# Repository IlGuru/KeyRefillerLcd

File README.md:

# KeyRefillerLcd
Progetto Key Refiller con LCD

KEY_REFILLER_LCD.X
  Cartella di lavoro di "Microchip MPLAB.X IDE" del firmware
Kicad
  Cartella di lavoro del progetto Kicad del PCB

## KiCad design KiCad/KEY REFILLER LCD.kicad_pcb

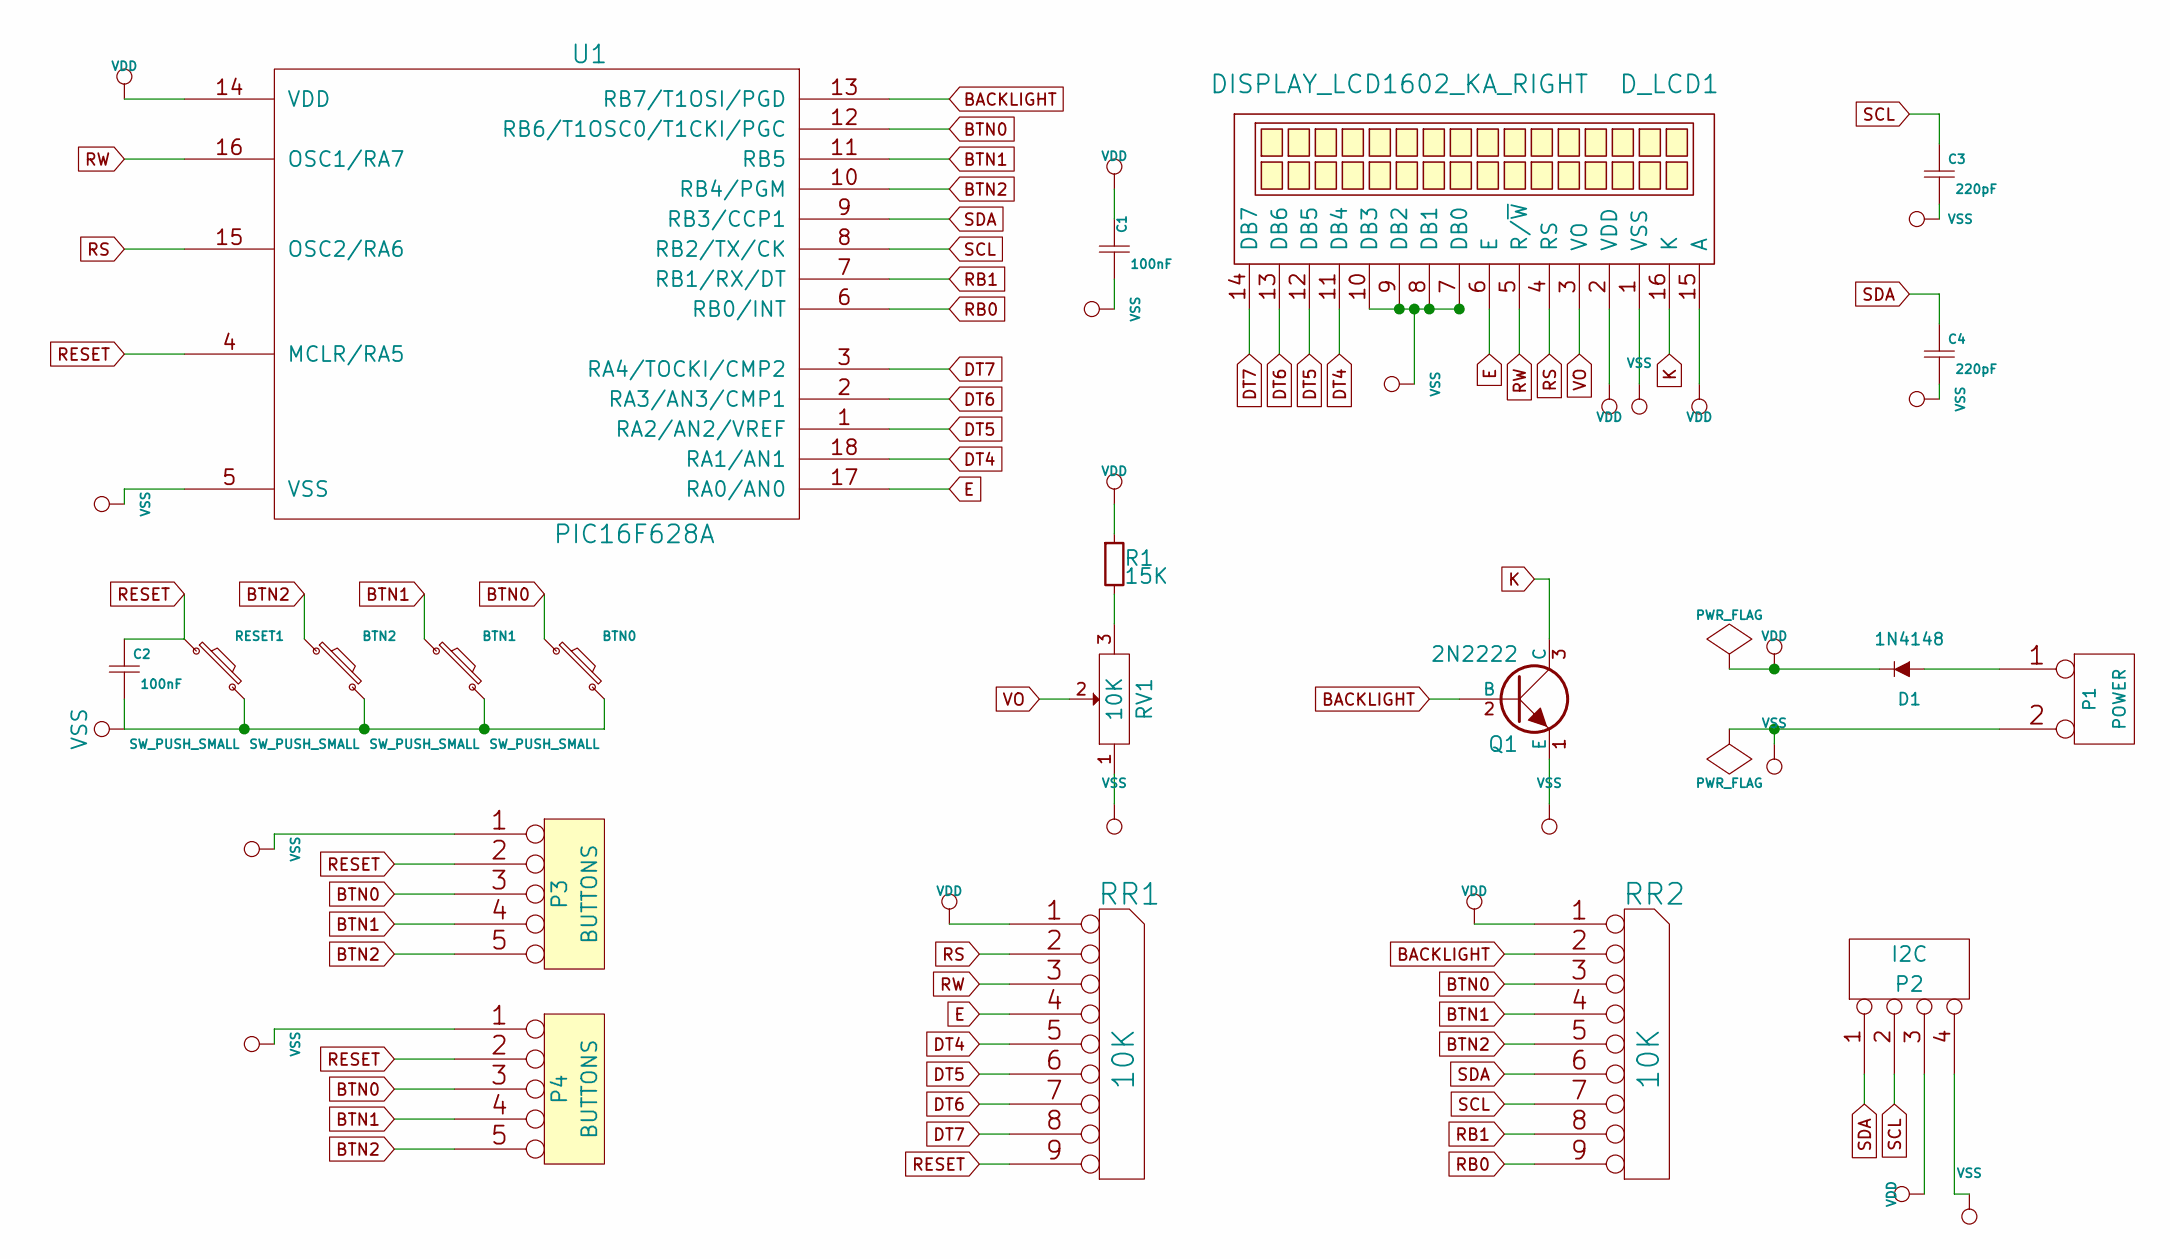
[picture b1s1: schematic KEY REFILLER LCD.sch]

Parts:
BTN0, BTN1, BTN2: SW_PUSH_SMALL
C1, C2: 100nF; C_Disc_D6_P5
C3, C4: 220pF; C_Disc_D6_P5
D1: 1N4148; Diode_DO-35_SOD27_Horizontal_RM10
D_LCD1: DISPLAY_LCD1602_KA_RIGHT; RC1602A
P1: POWER; Pin_Header_Straight_1x02
P2: I2C; Pin_Header_Straight_1x04
P3, P4: BUTTONS; Pin_Header_Straight_1x05
Q1: 2N2222; TO-18_3Pin
R1: 15K; Resistor_Horizontal_RM15mm
RESET1: SW_PUSH_SMALL
RR1, RR2: 10K; r_sil_9
RV1: 10K; POT_4x2
U1: PIC16F628A; DIP-18_W7.62mm_LongPads

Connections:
BACKLIGHT: Q1.2 (B), RR2.2, U1.13 (RB7/T1OSI/PGD)
BTN0: BTN0.1, P3.3, P4.3, RR2.3, U1.12 (RB6/T1OSC0/T1CKI/PGC)
BTN1: BTN1.1, P3.4, P4.4, RR2.4, U1.11 (RB5)
BTN2: BTN2.1, P3.5, P4.5, RR2.5, U1.10 (RB4/PGM)
DT4: D_LCD1.11 (DB4), RR1.5, U1.18 (RA1/AN1)
DT5: D_LCD1.12 (DB5), RR1.6, U1.1 (RA2/AN2/VREF)
DT6: D_LCD1.13 (DB6), RR1.7, U1.2 (RA3/AN3/CMP1)
DT7: D_LCD1.14 (DB7), RR1.8, U1.3 (RA4/TOCKI/CMP2)
E: D_LCD1.6 (E), RR1.4, U1.17 (RA0/AN0)
K: D_LCD1.16 (K), Q1.3 (C)
unnamed: D1.2 (A), P1.1
unnamed: R1.2, RV1.3
RB0: RR2.9, U1.6 (RB0/INT)
RB1: RR2.8, U1.7 (RB1/RX/DT)
RESET: C2.1, P3.2, P4.2, RESET1.1, RR1.9, U1.4 (MCLR/RA5)
RS: D_LCD1.4 (RS), RR1.2, U1.15 (OSC2/RA6)
RW: D_LCD1.5 (R/~W), RR1.3, U1.16 (OSC1/RA7)
SCL: C3.1, P2.2, RR2.7, U1.8 (RB2/TX/CK)
SDA: C4.1, P2.1, RR2.6, U1.9 (RB3/CCP1)
VDD: C1.1, D1.1 (K), D_LCD1.2 (VDD), D_LCD1.15 (A), P2.3, R1.1, RR1.1 (COM), RR2.1 (COM), U1.14 (VDD)
VO: D_LCD1.3 (VO), RV1.2
VSS: BTN0.2, BTN1.2, BTN2.2, C1.2, C2.2, C3.2, C4.2, D_LCD1.1 (VSS), D_LCD1.7 (DB0), D_LCD1.8 (DB1), D_LCD1.9 (DB2), D_LCD1.10 (DB3), P1.2 (PM), P2.4, P3.1, P4.1, Q1.1 (E), RESET1.2, RV1.1, U1.5 (VSS)

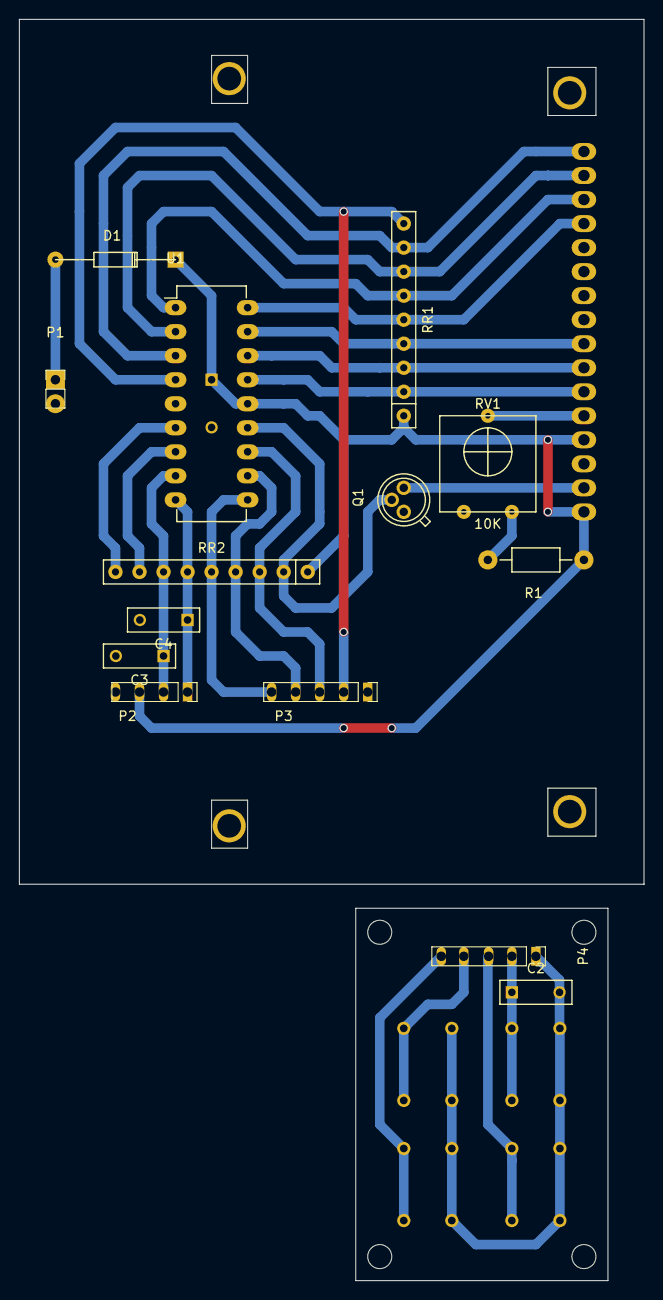
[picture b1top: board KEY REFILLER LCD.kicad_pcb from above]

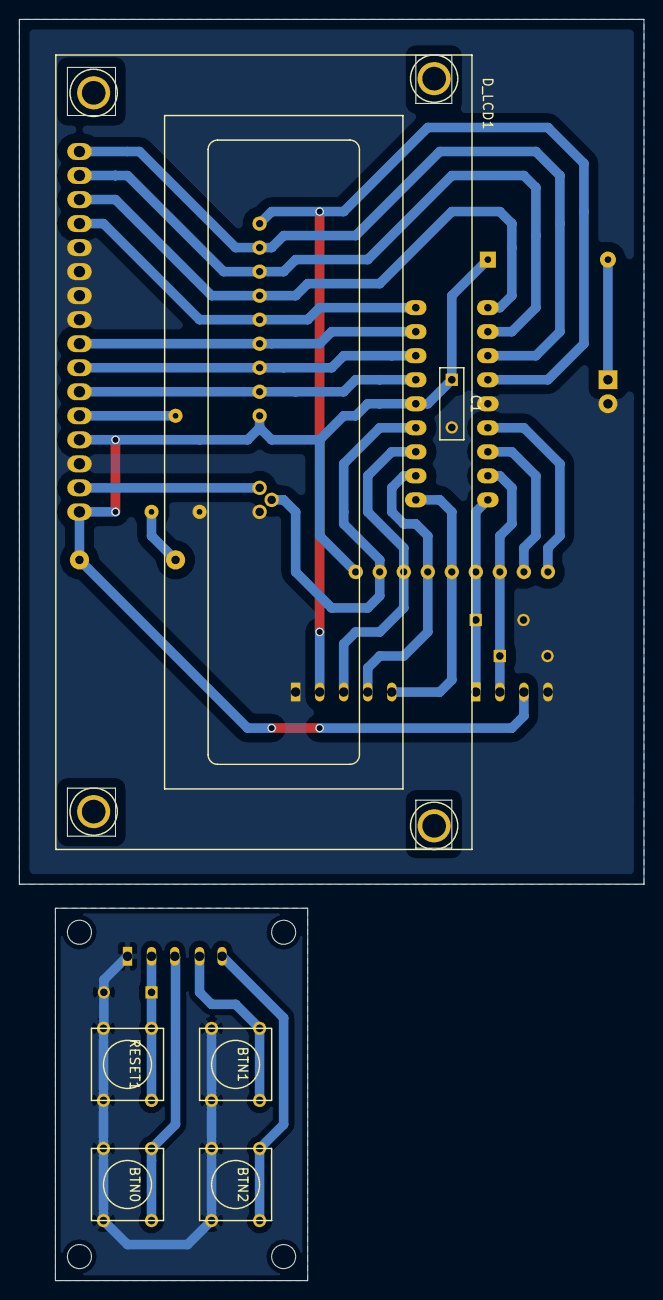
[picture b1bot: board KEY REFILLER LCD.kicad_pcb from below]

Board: 2 copper layers, 66.0 x 133.4 mm, 20 parts (6 on the bottom side), 22 nets.

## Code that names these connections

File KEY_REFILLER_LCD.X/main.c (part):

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//------------------------------------------------------------------------------

// CONFIG
#pragma config FOSC     = INTOSCIO  // Oscillator Selection bits (INTOSC oscillator: I/O function on RA6/OSC2/CLKOUT pin, I/O function on RA7/OSC1/CLKIN)
#pragma config WDTE     = OFF       // Watchdog Timer Enable bit (WDT disabled)
#pragma config PWRTE    = OFF       // Power-up Timer Enable bit (PWRT disabled)
#pragma config MCLRE    = ON        // RA5/MCLR/VPP Pin Function Select bit (RA5/MCLR/VPP pin function is digital input, MCLR internally tied to VDD)
#pragma config BOREN    = OFF       // Brown-out Detect Enable bit (BOD disabled)
#pragma config LVP      = OFF       // Low-Voltage Programming Enable bit (RB4/PGM pin has digital I/O function, HV on MCLR must be used for programming)
#pragma config CPD      = OFF       // Data EE Memory Code Protection bit (Data memory code protection off)
#pragma config CP       = OFF       // Flash Program Memory Code Protection bit (Code protection off)

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    //                0 = None of the RB<7:4> pins have changed state
        OPTION_REGbits.INTEDG	= 0;            // 	Interrupt on falling edge(1 is rising). Resistenze di pull-up sugli ingressi

        INTCONbits.INTE         = 0;            //  Disables the RB0/INT external interrupt
//        INTCONbits.INTE         = 1;            //  Enables the RB0/INT external interrupt

//        INTCONbits.RBIE         = 0;            //	Disables the RB port change interrupt
        INTCONbits.RBIE         = 1;            //	Enables the RB port change interrupt
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
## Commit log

2015-09-04 :circus_tent: Added .gitattributes & .gitignore files
2015-09-04 Primo commit
2015-09-04 Pulizia
